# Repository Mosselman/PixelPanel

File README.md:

https://github.com/Mosselman/PixelPanel/blob/main/Interface%20module/Code/platformCode/src/main.cpp

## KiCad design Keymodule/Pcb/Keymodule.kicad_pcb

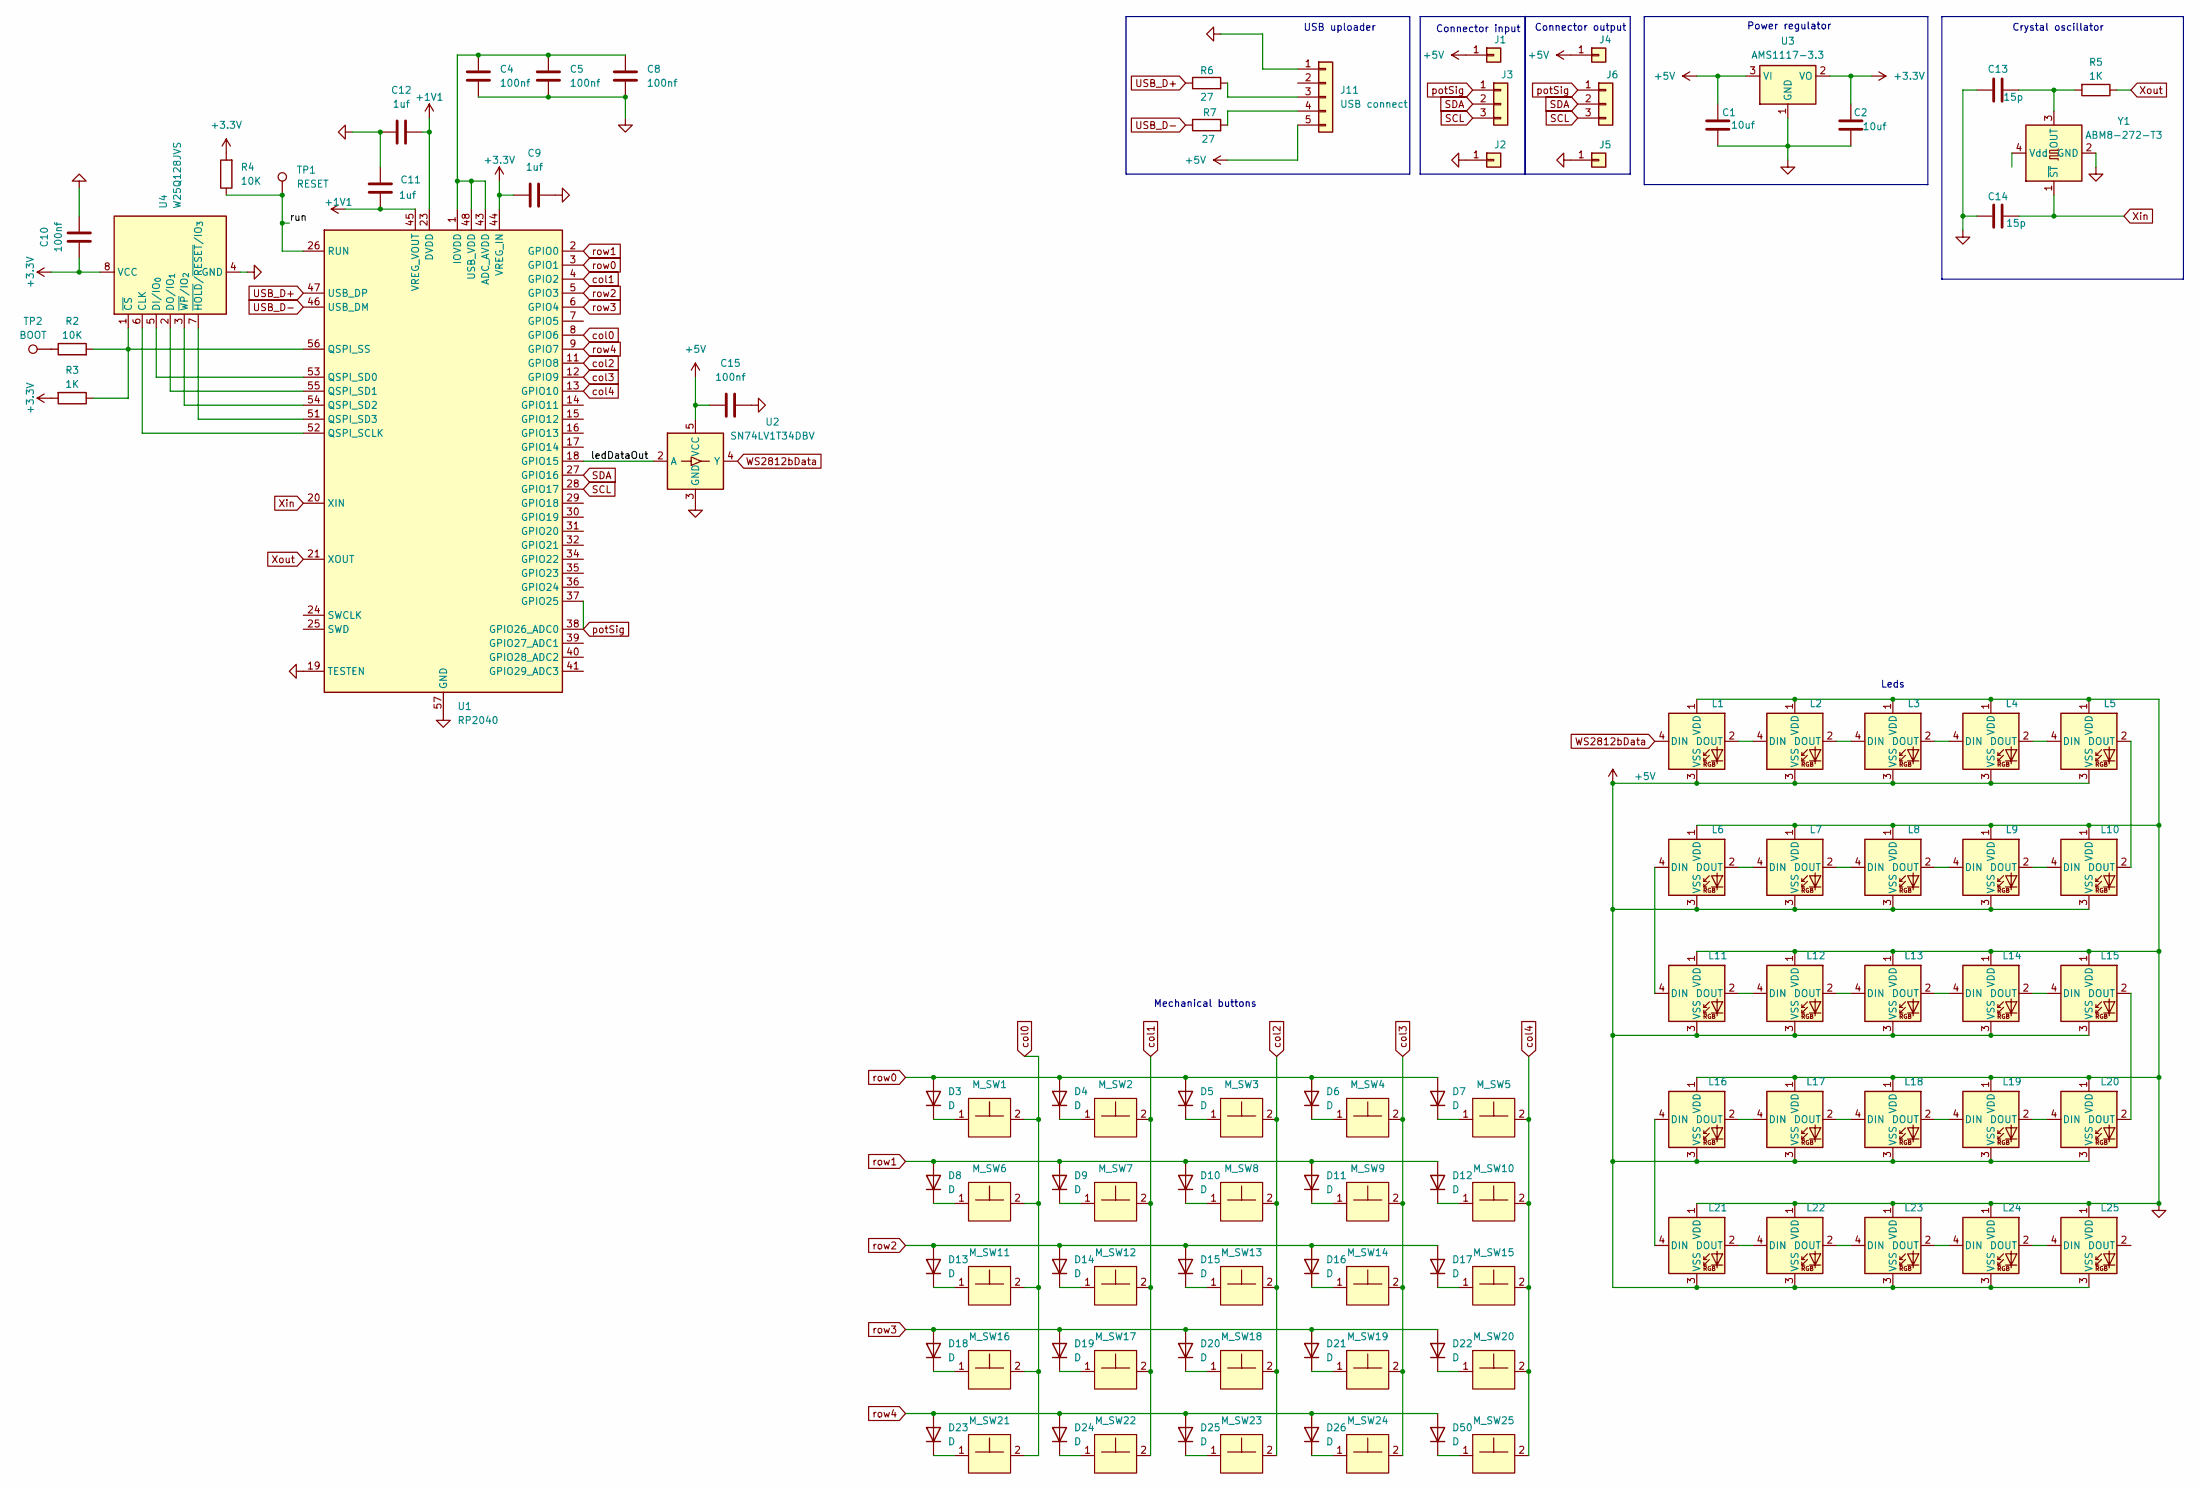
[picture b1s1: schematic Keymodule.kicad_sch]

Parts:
C1: 10uf; C_0805_2012Metric; part C88484
C2: 10uf; C_0805_2012Metric
C4: 100nf; C_0402_1005Metric; part C60474
C5, C8, C10, C15: 100nf; C_0402_1005Metric
C9: 1uf; C_0402_1005Metric; part C106254
C11, C12: 1uf; C_0402_1005Metric
C13: 15p; C_0402_1005Metric; part C106997
C14: 15p; C_0402_1005Metric
D3: D; D_0603_1608Metric; part C30584800
D4, D5, D6, D7, D8, D9, D10, D11, D12, D13, D14, D15, D16, D17, D18, D19, D20, D21, D22, D23, D24, D25, D26, D50: D; D_0603_1608Metric
J1, J2, J4, J5: Conn_01x01; PinHeader_1x01_P1.27mm_Horizontal
J3, J6: Conn_01x03; PinHeader_1x03_P2.54mm_Horizontal
J11: USB connect; PinSocket_1x05_P2.54mm_Vertical
L1, L2, L3, L4, L5, L6, L7, L8, L9, L10, L11, L12, L13, L14, L15, L16, L17, L18, L19, L20, L21, L22, L23, L24, L25: WS2812B; DY-S352818RGBC6812-2T led down
M_SW1, M_SW2, M_SW3, M_SW4, M_SW5, M_SW6, M_SW7, M_SW8, M_SW9, M_SW10, M_SW11, M_SW12, M_SW13, M_SW14, M_SW15, M_SW16, M_SW17, M_SW18, M_SW19, M_SW20, M_SW21, M_SW22, M_SW23, M_SW24, M_SW25: Kailh low profile Choc switch V1
R2: 10K; R_0402_1005Metric; part C60490
R3, R5: 1K; R_0402_1005Metric
R4: 10K; R_0402_1005Metric
R6, R7: 27; R_0402_1005Metric
TP1: RESET; TestPoint_Pad_D2.0mm
TP2: BOOT; TestPoint_Pad_D2.0mm
U1: RP2040; QFN-56-1EP_7x7mm_P0.4mm_EP3.2x3.2mm
U2: SN74LV1T34DBV; SOT-23-5; Part number SN74LV1T34DBVR-TP
U3: AMS1117-3.3; SOT-223-3_TabPin2
U4: W25Q128JVS; SOIC-8_5.3x5.3mm_P1.27mm
Y1: ABM8-272-T3; Oscillator_SMD_SiT_PQFN-4Pin_2.0x1.6mm

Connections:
+1V1: C11.1, C12.2, U1.23 (DVDD), U1.45 (VREG_VOUT), U1.50 (DVDD)
+3.3V: C2.2, C9.1, C10.2, R3.2, R4.2, U1.44 (VREG_IN), U3.2 (VO), U4.8 (VCC); also elsewhere on the board
+5V: C1.2, C15.1, J1.1, J4.1, J11.5, L1.3 (VSS), L2.3 (VSS), L3.3 (VSS), L4.3 (VSS), L5.3 (VSS), L6.3 (VSS), L7.3 (VSS), L8.3 (VSS), L9.3 (VSS), L10.3 (VSS), L11.3 (VSS), L12.3 (VSS), L13.3 (VSS), L14.3 (VSS), L15.3 (VSS), L16.3 (VSS), L17.3 (VSS), L18.3 (VSS), L19.3 (VSS), L20.3 (VSS), L21.3 (VSS), L22.3 (VSS), L23.3 (VSS), L24.3 (VSS), L25.3 (VSS), U2.5 (VCC), U3.3 (VI); also elsewhere on the board
/ledDataOut: U1.18 (GPIO15), U2.2 (A)
/run: R4.1, TP1.1, U1.26 (RUN); also elsewhere on the board
GND: C1.1, C2.1, C4.2, C5.2, C8.2, C9.2, C10.1, C11.2, C12.1, C13.1, C14.1, C15.2, J2.1, J5.1, J11.1, L1.1 (VDD), L2.1 (VDD), L3.1 (VDD), L4.1 (VDD), L5.1 (VDD), L6.1 (VDD), L7.1 (VDD), L8.1 (VDD), L9.1 (VDD), L10.1 (VDD), L11.1 (VDD), L12.1 (VDD), L13.1 (VDD), L14.1 (VDD), L15.1 (VDD), L16.1 (VDD), L17.1 (VDD), L18.1 (VDD), L19.1 (VDD), L20.1 (VDD), L21.1 (VDD), L22.1 (VDD), L23.1 (VDD), L24.1 (VDD), L25.1 (VDD), U1.19 (TESTEN), U1.57 (GND), U2.3 (GND), U3.1 (GND), U4.4 (GND), Y1.2 (GND), Y1.4 (Vdd); also elsewhere on the board
unnamed: D3.1 (K), M_SW1.1
unnamed: D4.1 (K), M_SW2.1
unnamed: D5.1 (K), M_SW3.1
unnamed: D6.1 (K), M_SW4.1
unnamed: D7.1 (K), M_SW5.1
unnamed: D8.1 (K), M_SW6.1
unnamed: D9.1 (K), M_SW7.1
unnamed: D10.1 (K), M_SW8.1
unnamed: D11.1 (K), M_SW9.1
unnamed: D12.1 (K), M_SW10.1
unnamed: D13.1 (K), M_SW11.1
unnamed: D14.1 (K), M_SW12.1
unnamed: D15.1 (K), M_SW13.1
unnamed: D16.1 (K), M_SW14.1
unnamed: D17.1 (K), M_SW15.1
unnamed: D18.1 (K), M_SW16.1
unnamed: D19.1 (K), M_SW17.1
unnamed: D20.1 (K), M_SW18.1
unnamed: D21.1 (K), M_SW19.1
unnamed: D22.1 (K), M_SW20.1
unnamed: D23.1 (K), M_SW21.1
unnamed: D24.1 (K), M_SW22.1
unnamed: D25.1 (K), M_SW23.1
unnamed: D26.1 (K), M_SW24.1
unnamed: D50.1 (K), M_SW25.1
unnamed: J11.3, R6.2
unnamed: J11.4, R7.2
unnamed: L1.2 (DOUT), L2.4 (DIN)
unnamed: L2.2 (DOUT), L3.4 (DIN)
unnamed: L3.2 (DOUT), L4.4 (DIN)
unnamed: L4.2 (DOUT), L5.4 (DIN)
unnamed: L6.2 (DOUT), L7.4 (DIN)
unnamed: L7.2 (DOUT), L8.4 (DIN)
unnamed: L8.2 (DOUT), L9.4 (DIN)
unnamed: L9.2 (DOUT), L10.4 (DIN)
unnamed: L5.2 (DOUT), L10.2 (DOUT)
unnamed: L6.4 (DIN), L11.4 (DIN)
unnamed: L11.2 (DOUT), L12.4 (DIN)
unnamed: L12.2 (DOUT), L13.4 (DIN)
unnamed: L13.2 (DOUT), L14.4 (DIN)
unnamed: L14.2 (DOUT), L15.4 (DIN)
unnamed: L15.2 (DOUT), L20.2 (DOUT)
unnamed: L16.4 (DIN), L21.4 (DIN)
unnamed: L16.2 (DOUT), L17.4 (DIN)
unnamed: L17.2 (DOUT), L18.4 (DIN)
unnamed: L18.2 (DOUT), L19.4 (DIN)
unnamed: L19.2 (DOUT), L20.4 (DIN)
unnamed: L21.2 (DOUT), L22.4 (DIN)
unnamed: L22.2 (DOUT), L23.4 (DIN)
unnamed: L23.2 (DOUT), L24.4 (DIN)
unnamed: L24.2 (DOUT), L25.4 (DIN)
unnamed 57: R2.1, TP2.1; also elsewhere on the board
unnamed 58: C4.1, C5.1, C8.1, U1.1 (IOVDD), U1.10 (IOVDD), U1.22 (IOVDD), U1.33 (IOVDD), U1.42 (IOVDD), U1.43 (ADC_AVDD), U1.48 (USB_VDD), U1.49 (IOVDD); also elsewhere on the board
unnamed: U1.52 (QSPI_SCLK), U4.6 (CLK)
unnamed: U1.53 (QSPI_SD0), U4.5 (DI/IO_{0})
unnamed: U1.55 (QSPI_SD1), U4.2 (DO/IO_{1})
unnamed: U1.54 (QSPI_SD2), U4.3 (~WP/IO_{2})
unnamed: U1.51 (QSPI_SD3), U4.7 (~HOLD/~RESET/IO_{3})
unnamed 64: R2.2, R3.1, U1.56 (QSPI_SS), U4.1 (~CS); also elsewhere on the board
unnamed: C13.2, R5.2, Y1.3 (OUT)
SCL: J3.3, J6.3, U1.28 (GPIO17)
SDA: J3.2, J6.2, U1.27 (GPIO16)
USB_D+: R6.1, U1.47 (USB_DP)
USB_D-: R7.1, U1.46 (USB_DM)
WS2812bData: L1.4 (DIN), U2.4 (Y)
Xin: C14.2, U1.20 (XIN), Y1.1 (~ST)
Xout: R5.1, U1.21 (XOUT)
col0: M_SW1.2, M_SW6.2, M_SW11.2, M_SW16.2, M_SW21.2, U1.8 (GPIO6)
col1: M_SW2.2, M_SW7.2, M_SW12.2, M_SW17.2, M_SW22.2, U1.4 (GPIO2)
col2: M_SW3.2, M_SW8.2, M_SW13.2, M_SW18.2, M_SW23.2, U1.11 (GPIO8)
col3: M_SW4.2, M_SW9.2, M_SW14.2, M_SW19.2, M_SW24.2, U1.12 (GPIO9)
col4: M_SW5.2, M_SW10.2, M_SW15.2, M_SW20.2, M_SW25.2, U1.13 (GPIO10)
potSig: J3.1, J6.1, U1.37 (GPIO25), U1.38 (GPIO26_ADC0)
row0: D3.2 (A), D4.2 (A), D5.2 (A), D6.2 (A), D7.2 (A), U1.3 (GPIO1)
row1: D8.2 (A), D9.2 (A), D10.2 (A), D11.2 (A), D12.2 (A), U1.2 (GPIO0)
row2: D13.2 (A), D14.2 (A), D15.2 (A), D16.2 (A), D17.2 (A), U1.5 (GPIO3)
row3: D18.2 (A), D19.2 (A), D20.2 (A), D21.2 (A), D22.2 (A), U1.6 (GPIO4)
row4: D23.2 (A), D24.2 (A), D25.2 (A), D26.2 (A), D50.2 (A), U1.9 (GPIO7)

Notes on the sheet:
Leds
Crystal oscillator
USB uploader
Connector output
Mechanical buttons
Connector input
Power regulator

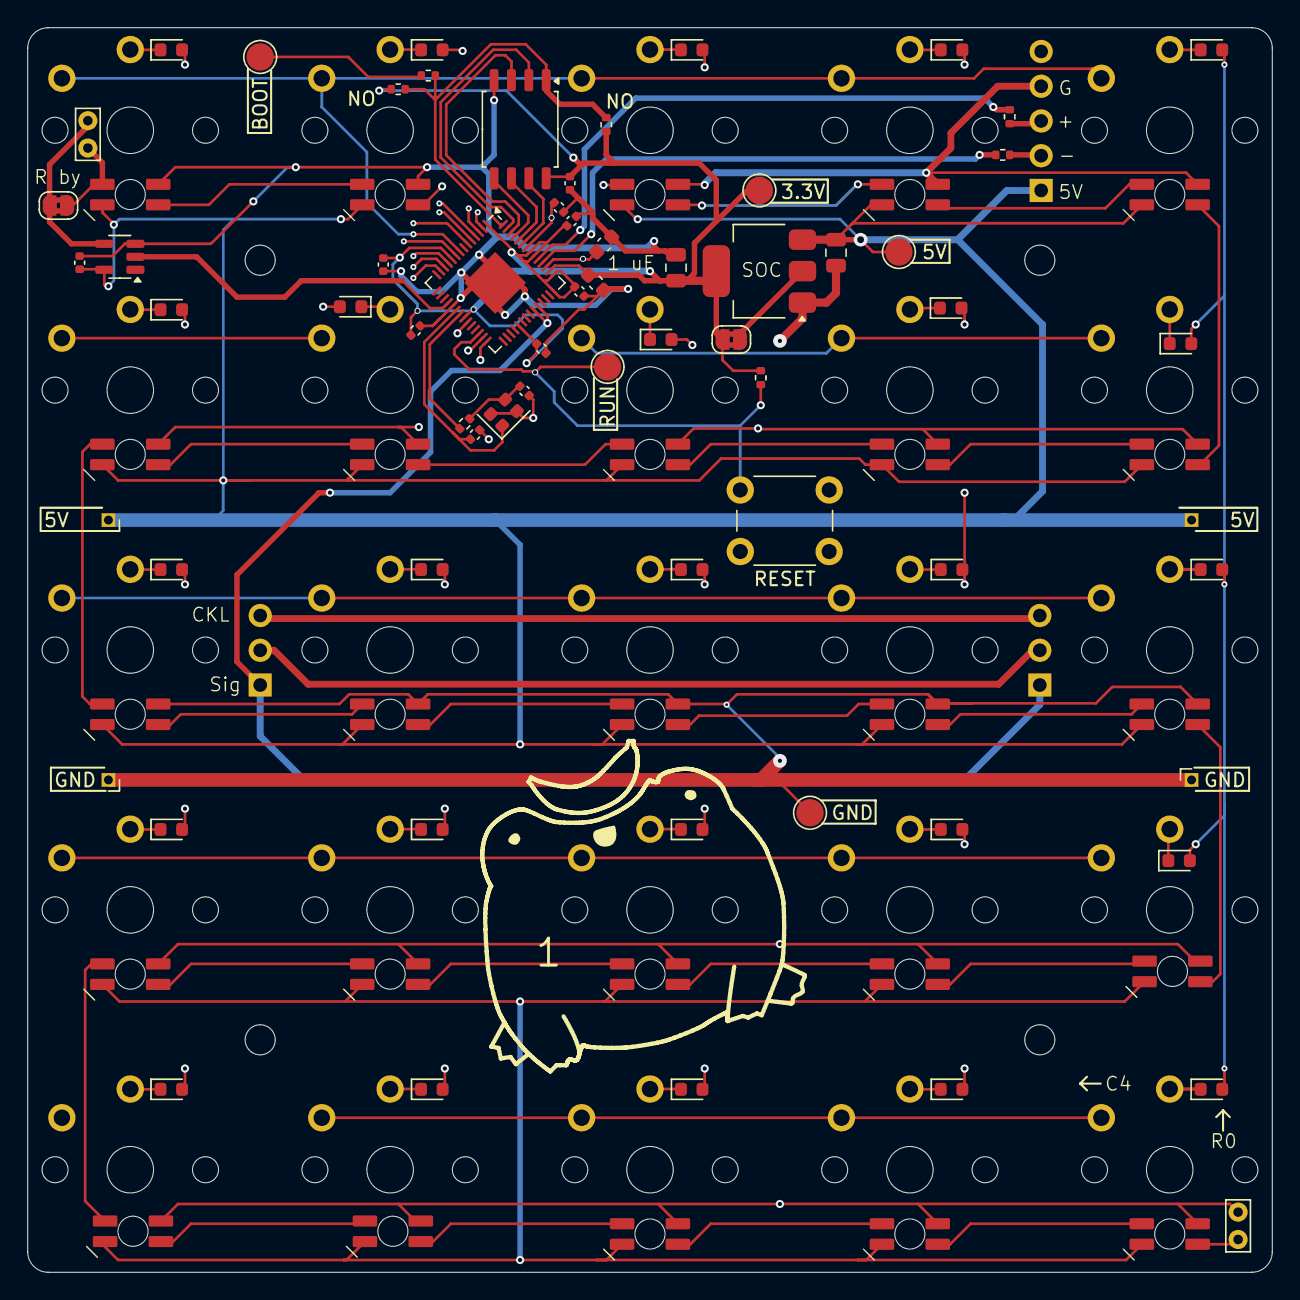
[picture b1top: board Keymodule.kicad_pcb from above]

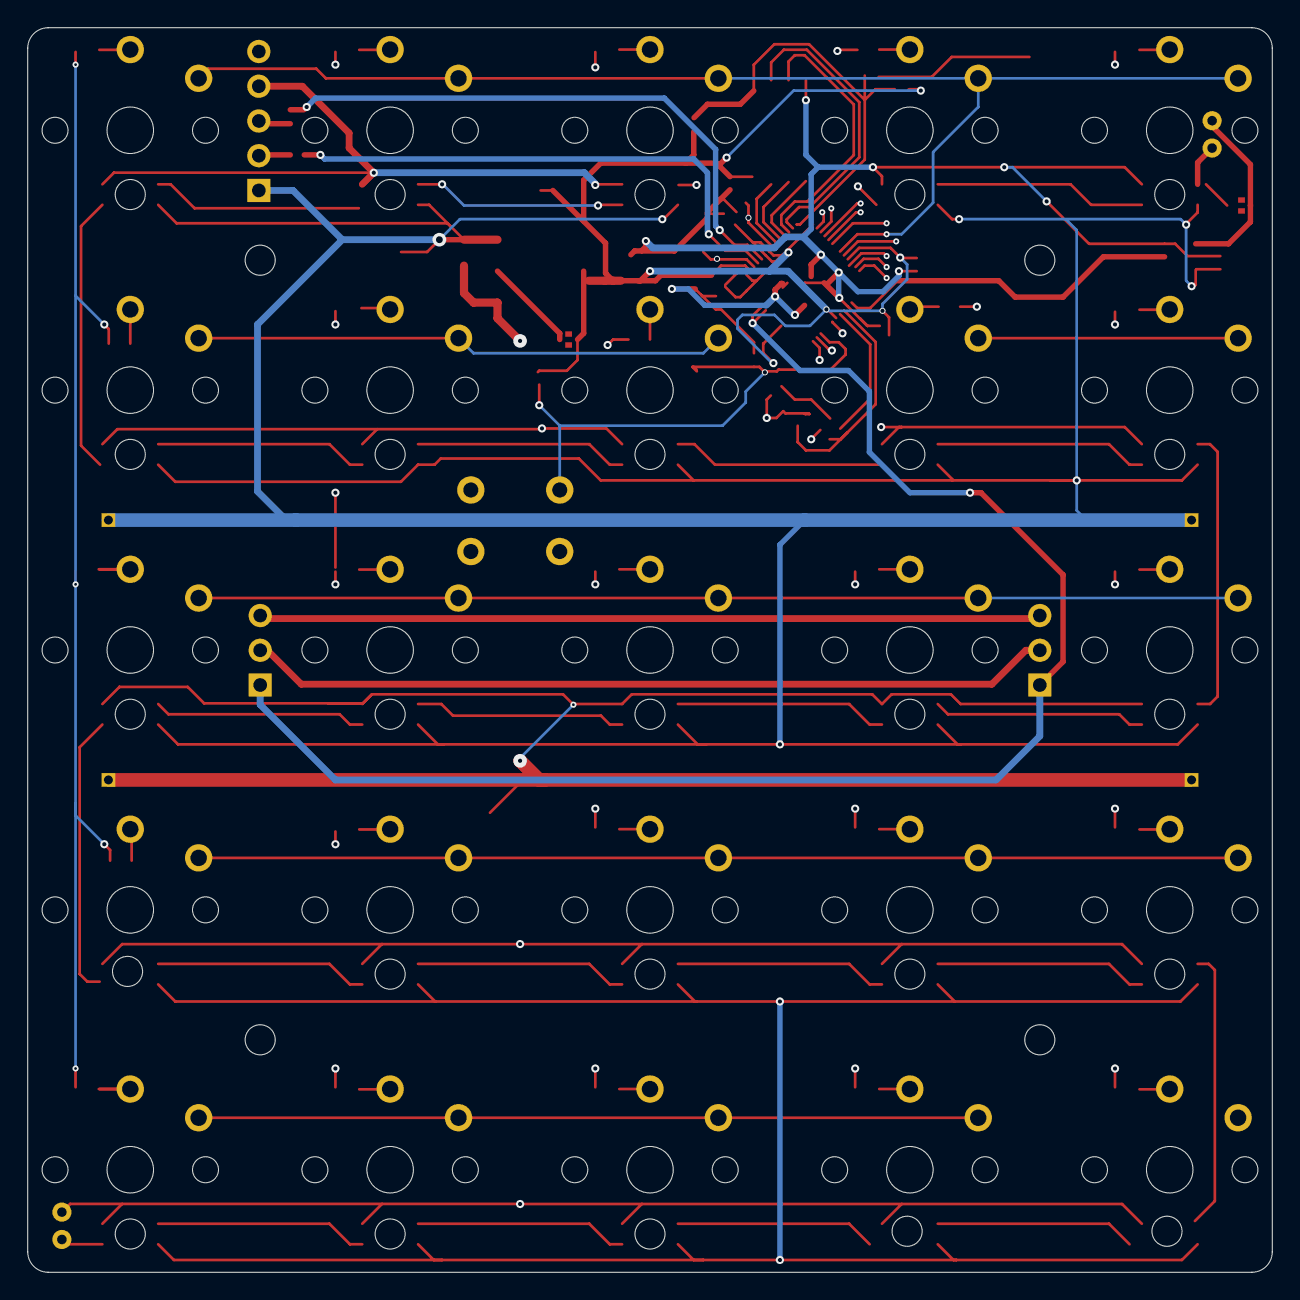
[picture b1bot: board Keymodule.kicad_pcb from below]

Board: 4 copper layers, 91.0 x 91.0 mm, 111 parts (26 on the bottom side), 82 nets.

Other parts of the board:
3.3V, 5V#3: TestPoint_Pad_D2.0mm
5V, 5V#2: Conn_01x01; PinHeader_1x01_P1.27mm_Horizontal
BOOT: BOOT; TestPoint_Pad_D2.0mm
C4#2, C4#3: 100nf; C_0402_1005Metric
GND: Conn_01x01; PinHeader_1x01_P1.27mm_Horizontal
GND#2: TestPoint_Pad_D2.0mm
GND#3: Conn_01x01; PinHeader_1x01_P1.27mm_Horizontal
NO: 10K DNF; R_0402_1005Metric
NO#2: 1K; R_0402_1005Metric
RESET: SW_PUSH_6mm
RUN: RESET; TestPoint_Pad_D2.0mm

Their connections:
+3.3V: 3.3V.1, NO.2, NO#2.2; also elsewhere on the board
+5V: 5V.1, 5V#2.1, 5V#3.1; also elsewhere on the board
/run: RESET.2, RUN.1; also elsewhere on the board
GND: C4#2.2, C4#3.2, GND.1, GND#2.1, GND#3.1, RESET.1; also elsewhere on the board
unnamed 57: BOOT.1; also elsewhere on the board
unnamed 58: C4#2.1, C4#3.1; also elsewhere on the board
unnamed 64: NO.1, NO#2.1; also elsewhere on the board

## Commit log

2026-01-12 First upload
    Still need to clean files
2026-01-14 Added traces to buttons
2026-01-15 Stared wiring ic
    LED signal boost not done
    But its a start
2026-01-19 Wired main power caps but to little space
2026-01-23 Getting there (4 layers)
    Made the switch to a 4 layer PCB.
    het is iets duurder maar wel de moeite waard.
2026-01-24 Almost done
2026-01-25 Led's & buttons are done
    Still need to optimize and check MCU connections
2026-01-29 Better final version
2026-02-02 Backup before auto cleanup
2026-02-08 Created main SW assembly
    still needs lots of work
2026-02-08 Little ajustment of cad
2026-02-14 Ihope this is the one
2026-02-15 Keymodule ready to order
2026-02-16 PCB is orderd !
2026-02-23 Re-did folder layout
    Keymodule and Interface module now have separte files
2026-03-03 changes to interface module circuit and a bit of vibe coding
2026-03-03 Finally PlatformIO works
2026-03-15 Working on the brainmoduel code
2026-03-15 Main layout is set up still needs lots of work
2026-03-15 Update README to reflect module location
2026-03-15 add link test
2026-04-25 Added the First CODE!!!! the pcb working now
2026-04-25 Test code exported uf2 type file
2026-05-02 Made 2nd verstion for pcb keep this as backup
